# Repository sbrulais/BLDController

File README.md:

# BLDController
Simple sensored BLDC motor controller

This controller fits into a 40x50mm board:

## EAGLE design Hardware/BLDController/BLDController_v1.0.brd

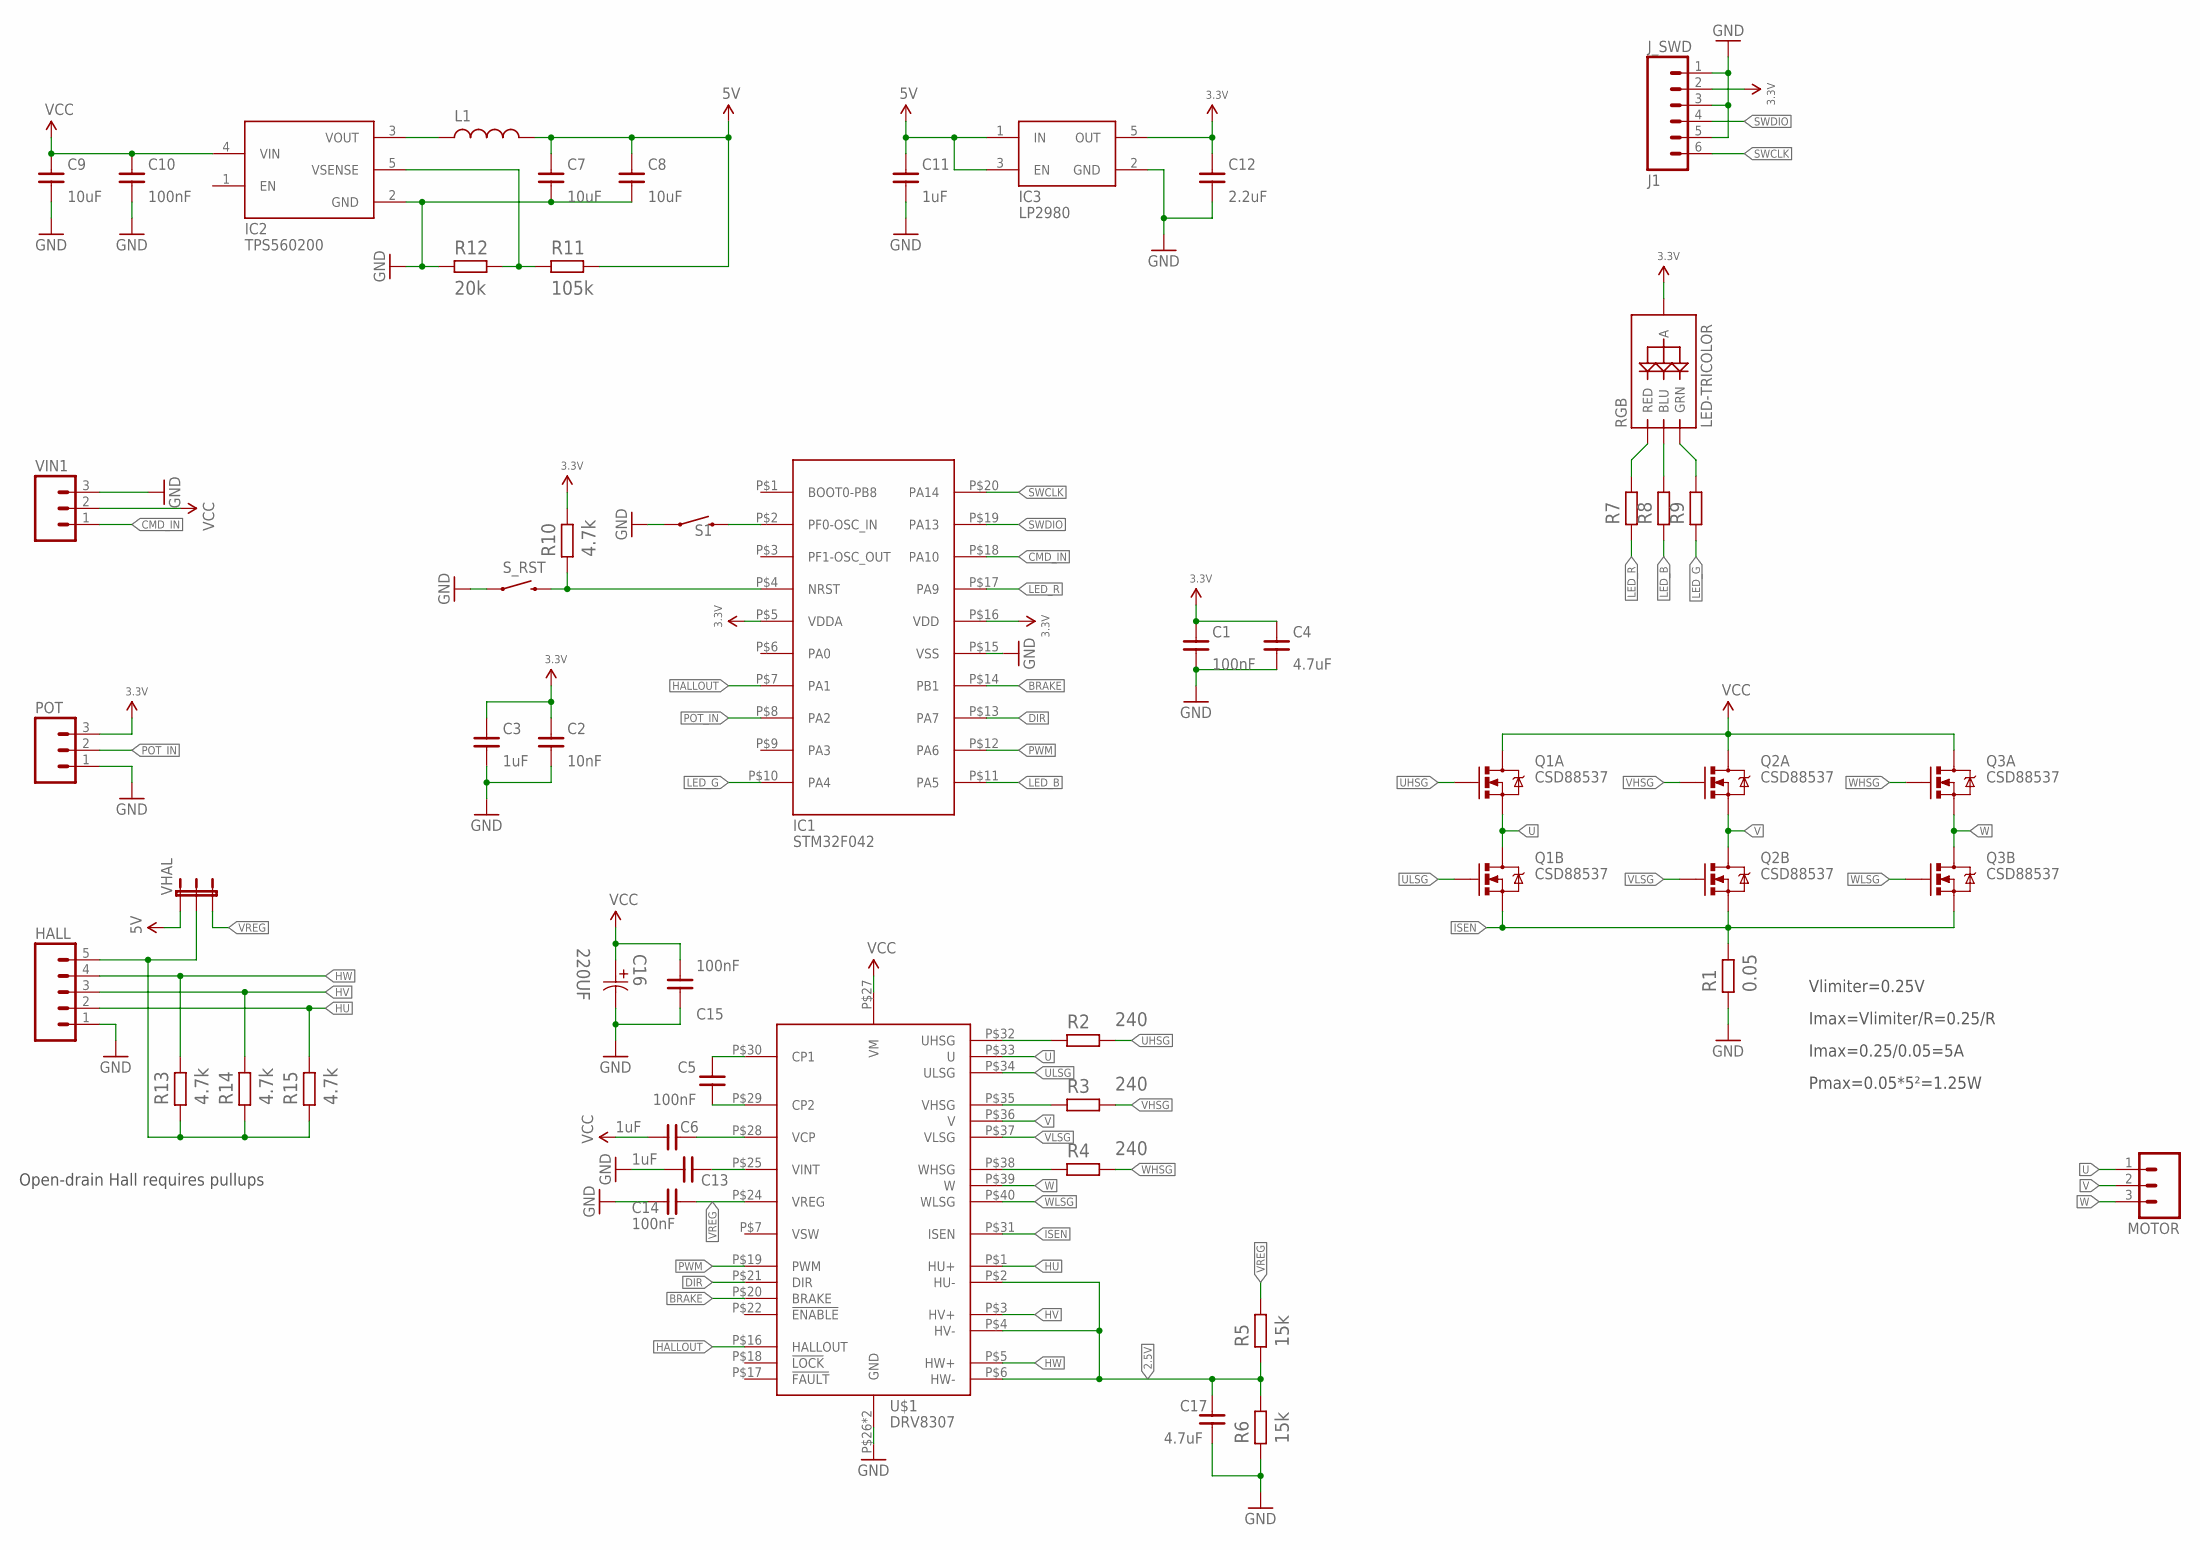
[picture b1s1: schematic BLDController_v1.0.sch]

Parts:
C1, C5, C10, C14, C15: 100nF; R0603
C2: 10nF; R0603
C3, C6, C11, C13: 1uF; R0805
C4: 4.7uF; R0805
C7, C8: 10uF; R0805
C9: 10uF; 1206
C12: 2.2uF; R0805
C16: 220UF; CAPPR500-1000X3200
C17: 4.7uF; R0603
HALL: M05SCREW; SCREWTERMINAL-3.5MM-5
IC1: STM32F042; TSSOP20
IC2: TPS560200; SOT23-5L
IC3: LP2980; SOT23-5L
J1: J_SWD; ZIF-06-1MM
L1: LNRG_4026; NRG_4026
MOTOR: M03-SCREW-5MM; SCREWTERMINAL-5MM-3
POT: M03SCREW; SCREWTERMINAL-3.5MM-3
Q1, Q2, Q3: CSD88537; SO-08
R1: 0.05; CRF2512
R2, R3, R4: 240; R0603
R5, R6: 15k; R0603
R7, R8, R9: R0603
R10, R13, R14, R15: 4.7k; R0603
R11: 105k; R0603
R12: 20k; R0603
RGB: LED-TRICOLOR; PLCC4
S1: SWITCH-MOMENTARY-2SMD-3; TACTILE_SWITCH_SMD-3
S_RST: SWITCH-MOMENTARY-2SMD-3; TACTILE_SWITCH_SMD-3
U$1: DRV8307; PVQFN-N40
VHAL: JUMPER-3SMD; SJ_3
VIN1: M03SCREW; SCREWTERMINAL-3.5MM-3

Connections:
2.5V: C17.2, R5.1, R6.2, U$1.P$2 (HU-), U$1.P$4 (HV-), U$1.P$6 (HW-)
3.3V: C1.2, C2.2, C3.2, C4.2, C12.2, IC1.P$5 (VDDA), IC1.P$16 (VDD), IC3.5 (OUT), J1.2, POT.3, R10.2, RGB.P$1 (A)
5V: C7.2, C8.2, C11.2, IC3.1 (IN), IC3.3 (EN), L1.P$2 (2), R11.2, VHAL.1
BRAKE: IC1.P$14 (PB1), U$1.P$20 (BRAKE)
CMD_IN: IC1.P$18 (PA10), VIN1.1
DIR: IC1.P$13 (PA7), U$1.P$21 (DIR)
GND: C1.1, C2.1, C3.1, C4.1, C7.1, C8.1, C9.1, C10.1, C11.1, C12.1, C13.1, C14.2, C15.2, C16.2, C17.1, HALL.1, IC1.P$15 (VSS), IC2.2 (GND), IC3.2 (GND), J1.1, J1.3, J1.5, POT.1, R1.P$1 (1), R6.1, R12.1, S1.1, S_RST.1, U$1.P$26 (GND), U$1.PAD (GND), VIN1.3
HALLOUT: IC1.P$7 (PA1), U$1.P$16 (HALLOUT)
HU: HALL.2, R15.2, U$1.P$1 (HU+)
HV: HALL.3, R14.2, U$1.P$3 (HV+)
HW: HALL.4, R13.2, U$1.P$5 (HW+)
ISEN: Q1.3 (S), Q2.3 (S), Q3.3 (S), R1.P$2 (2), U$1.P$31 (ISEN)
LED_B: IC1.P$11 (PA5), R8.1
LED_G: IC1.P$10 (PA4), R9.1
LED_R: IC1.P$17 (PA9), R7.1
unnamed: C5.2, U$1.P$30 (CP1)
unnamed: C5.1, U$1.P$29 (CP2)
unnamed: C13.2, U$1.P$25 (VINT)
unnamed: C6.2, U$1.P$28 (VCP)
unnamed: R4.1, U$1.P$38 (WHSG)
unnamed: R7.2, RGB.P$4 (RED)
unnamed: R8.2, RGB.P$2 (BLU)
unnamed: R9.2, RGB.P$3 (GRN)
unnamed: R2.1, U$1.P$32 (UHSG)
unnamed: R3.1, U$1.P$35 (VHSG)
unnamed: IC1.P$4 (NRST), R10.1, S_RST.4 (2)
unnamed: IC2.3 (VOUT), L1.P$1 (1)
unnamed: IC2.5 (VSENSE), R11.1, R12.2
POT_IN: IC1.P$8 (PA2), POT.2
PWM: IC1.P$12 (PA6), U$1.P$19 (PWM)
SW1: IC1.P$2 (PF0-OSC_IN), S1.4 (2)
SWCLK: IC1.P$20 (PA14), J1.6
SWDIO: IC1.P$19 (PA13), J1.4
U: MOTOR.1, Q1.1 (S), Q1.5 (D), Q1.6 (D), U$1.P$33 (U)
UHSG: Q1.2 (G), R2.2
ULSG: Q1.4 (G), U$1.P$34 (ULSG)
V: MOTOR.2, Q2.1 (S), Q2.5 (D), Q2.6 (D), U$1.P$36 (V)
VCC: C6.1, C9.2, C10.2, C15.1, C16.1, IC2.4 (VIN), Q1.7 (D), Q1.8 (D), Q2.7 (D), Q2.8 (D), Q3.7 (D), Q3.8 (D), U$1.P$27 (VM), VIN1.2
VHALL: HALL.5, R13.1, R14.1, R15.1, VHAL.2
VHSG: Q2.2 (G), R3.2
VLSG: Q2.4 (G), U$1.P$37 (VLSG)
VREG: C14.1, R5.2, U$1.P$24 (VREG), VHAL.3
W: MOTOR.3, Q3.1 (S), Q3.5 (D), Q3.6 (D), U$1.P$39 (W)
WHSG: Q3.2 (G), R4.2
WLSG: Q3.4 (G), U$1.P$40 (WLSG)

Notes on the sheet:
Open-drain Hall requires pullups
Vlimiter=0.25V
Imax=Vlimiter/R=0.25/R
Imax=0.25/0.05=5A
Pmax=0.05*5²=1.25W

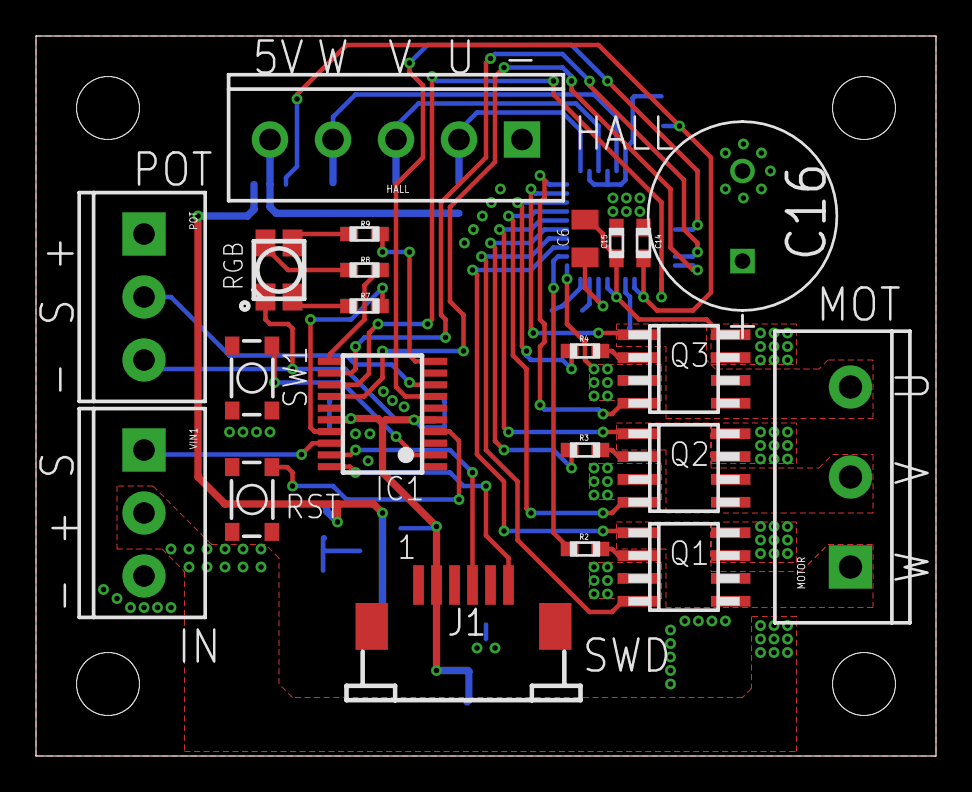
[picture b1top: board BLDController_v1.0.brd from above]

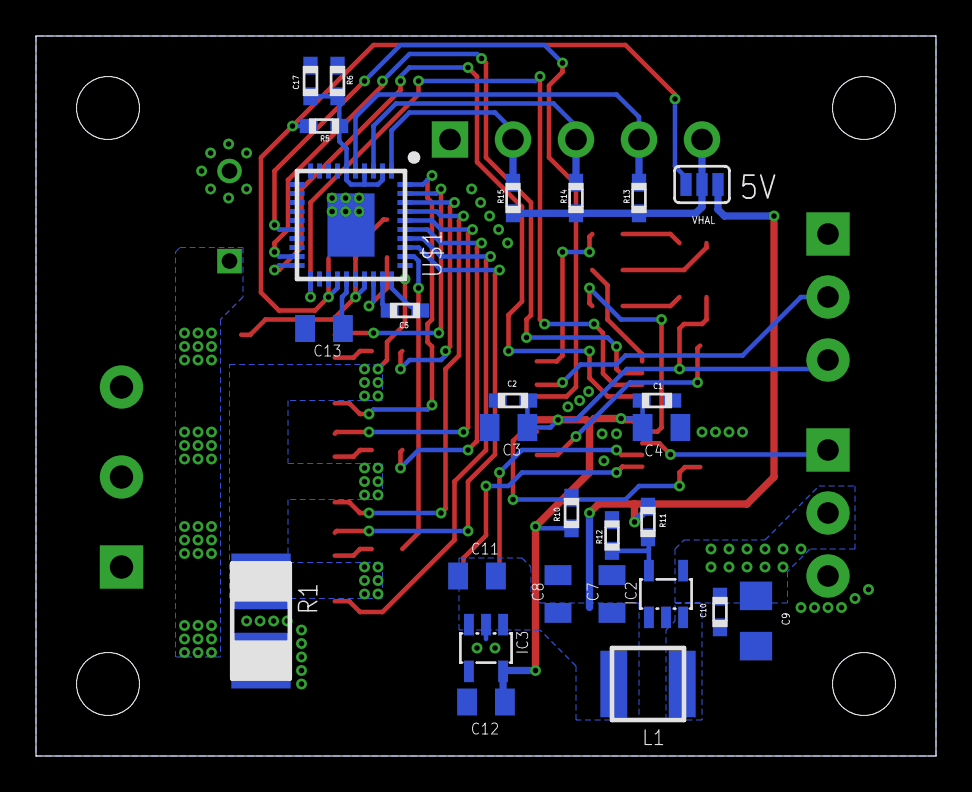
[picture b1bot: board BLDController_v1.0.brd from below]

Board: 2 copper layers, 50.0 x 40.0 mm, 49 parts (27 on the bottom side), 45 nets.

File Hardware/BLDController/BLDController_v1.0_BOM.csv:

Cmd;Qty;Value;Device;Package;Parts;Description
;1;;JUMPER-3SMD;SJ_3;VHAL;
;1;;LNRG_4026;NRG_4026;L1;
;1;;M03-SCREW-5MM;SCREWTERMINAL-5MM-3;MOTOR;Header 3
;2;;M03SCREW;SCREWTERMINAL-3.5MM-3;POT, VIN1;Header 3
;1;;M05SCREW;SCREWTERMINAL-3.5MM-5;HALL;Header 5
;3;;R0603;R0603;R7, R8, R9;
;2;;SWITCH-MOMENTARY-2SMD-3;TACTILE_SWITCH_SMD-3;S1, S_RST;Various NO switches- pushbuttons, reed, etc
;1; 220UF;C_PANAFC1V221-P5.0-D10;CAPPR500-1000X3200;C16;Aluminum Electrolytic Capacitors
;1;0.05;R2512;CRF2512;R1;
;5;100nF;C0603;R0603;C1, C5, C10, C14, C15;
;1;105k;R0603;R0603;R11;
;1;10nF;C0603;R0603;C2;
;2;10uF;C0805;R0805;C7, C8;
;1;10uF;C1206;1206;C9;
;2;15k;R0603;R0603;R5, R6;
;4;1uF;C0805;R0805;C3, C6, C11, C13;
;1;2.2uF;C0805;R0805;C12;
;1;20k;R0603;R0603;R12;
;3;240;R0603;R0603;R2, R3, R4;
;4;4.7k;R0603;R0603;R10, R13, R14, R15;
;1;4.7uF;C0603;R0603;C17;
;1;4.7uF;C0805;R0805;C4;
Ti;3;CSD88537;CSD88537;SO-08;Q1, Q2, Q3;
Ti;1;DRV8307;DRV8307;PVQFN-N40;U$1;
;1;J_SWD;ZIF-06-1MM;ZIF-06-1MM;J1;
;1;LED-TRICOLOR;LED-TRICOLOR;PLCC4;RGB;Tri-Color LED SMD
Ti;1;LP2980;LP2980;SOT23-5L;IC3;
;1;STM32F042;STM32F042;TSSOP20;IC1;ARM®-based 32-bit MCU, up to 32 KB Flash, crystal-less USB
Ti;1;TPS560200;TPS560200;SOT23-5L;IC2;

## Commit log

2015-09-20 Added Gitignore file
2015-10-07 Hardware V1 release
2015-12-04 Added BOM

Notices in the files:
parts and their libraries:
SparkFun-Electromechanical: Licensing: Creative Commons ShareAlike 4.0 International - https://creativecommons.org/licenses/by-sa/4.0
